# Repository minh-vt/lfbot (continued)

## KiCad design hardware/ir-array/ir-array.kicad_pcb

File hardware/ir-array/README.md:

# IR array — tám mắt, dải cong IR-03

> **Thiết kế PCB đã dừng theo [ADR-019](../../docs/decisions/ADR-019-module-based-hardware.md).** Nội dung bên dưới là lịch sử, không phải hướng dẫn lắp hiện hành. Dùng [pin map module](../wiring.md); không gia công hoặc đấu dây theo bảng cũ. Giữ source và thư viện chờ duyệt cleanup.

**IR-03 placement được người dùng duyệt G1 ngày 2026-10-19; chưa phát hành gia công.** Hai vai bo tròn, không tai đầu/bậc giữa; header đực 1×12 gần mép trong; giữ8 TCRT5000 và mạch headroom IR-02. Schematic giữ nguyên. Outline option02 đã được khớp lại vào footprint native qua KiCad IPC; placement sensor/header không đổi. Board nguồn chưa route. Một recovery candidate bị đổi thành bản có218 cung tròn và35 lỗi DRC; đã tái tạo bản sạch rồi thử reroute riêng +3V3, tăng margin +3V3 từ0.592 lên0.9005mm. Nhưng bản thử thêm3 via-in-pad SMD và EMC analyzer báo GP-001 regression cho /IR1; dù native DRC0 lỗi/0 unconnected, bản này **không được chọn làm candidate tốt hơn hoặc nhập vào nguồn**. Track /IR7 vẫn0.700mm; còn26 board warnings/42 parity warnings. Xem [review và log quyết định](OPTIMIZATION_REVIEW.md), [lịch sử outline/routing](REVIEW.md). G2/fabrication chưa duyệt.

Yêu cầu hiện tại: tám TCRT5000 trên một cung trong mặt phẳng PCB, các mặt đọc
cùng hướng xuống sàn và cùng độ cao; tối ưu diện tích PCB. Người dùng đã chốt
hai PCB tự thiết kế, **rời vật lý**: thân và đầu IR cong. Không còn ưu tiên
một PCB liền của M02. Cách gá theo [spec](../SPEC.md) và [tickets](../TICKETS.md),
chưa freeze trong bản CAD này. Gá caster in 3D do người dùng thiết kế.
BOM mua hàng vẫn là [HARDWARE_BOM.csv](../../docs/HARDWARE_BOM.csv).

## Giao diện tám mắt đã chọn

J1=`PinHeader_1x12_P2.54mm_Vertical` (header đực thẳng, 1×12). Số chân dưới đây là số pad,
không phải thứ tự nhìn từ đầu dây. Header không có khóa; đánh dấu pad1 ở cả hai
đầu và continuity-test harness trước cấp nguồn, không đoán theo màu dây. Bảng
GPIO dưới đây khớp netlist [MAIN hiện tại](../main/main.kicad_sch), với số chân
DevKitC-1 tham chiếu; chưa xác minh pinout/nguồn của TDM2533 thực tế hoặc
firmware. Không coi bảng là dây robot đã được đấu thử.

| J1 IR | Net | GPIO / ADC1 | Header DevKit chuẩn |
|---|---|---|---|
| 1 | +5V | Nguồn LED từ buck; không nối ADC | J1.21 (rail5V; phải kiểm tra backfeed hệ thống) |
| 2 | +3V3 | Nguồn pull-up từ DevKit | J1.1 hoặc J1.2 |
| 3 | GND | Ground chung | J1.22 hoặc J3.1 |
| 4 | LED_EN | GPIO21, active high | J3.18 |
| 5 | IR0 | GPIO1 / CH0 | J3.4 |
| 6 | IR1 | GPIO2 / CH1 | J3.5 |
| 7 | IR2 | GPIO4 / CH3 | J1.4 |
| 8 | IR3 | GPIO5 / CH4 | J1.5 |
| 9 | IR4 | GPIO6 / CH5 | J1.6 |
| 10 | IR5 | GPIO7 / CH6 | J1.7 |
| 11 | IR6 | GPIO8 / CH7 | J1.12 |
| 12 | IR7 | GPIO9 / CH8 | J1.15 |

BAT_ADC dành GPIO10/ADC1_CH9, headerJ1.16, **không đi qua cáp IR**. Đưa nó
vào cùng pattern continuous gồm9 kênh; không chạy oneshot trên ADC1 đang
continuous. Không dùng ADC2 DMA hoặc GPIO3 cho IR/BAT. MAIN để GPIO19/20
cho USB; không dùng GPIO0/3/45/46 và GPIO35…37 dành cho bộ nhớ Octal.
GPIO11…14 điều khiển hai A4950; GPIO15…18 tới cầu encoder R12…R15 mặc định
DNP. I²C dùng GPIO39/38 qua J5.3/J5.4; GPIO42/41 ra J5.5/J5.6. Đối chiếu
pinout module ToF trước khi đấu. GPIO38 có thể nối RGB LED trên một số
DevKit; phải xác nhận revision TDM2533, không bật LED trên chân đang dùng
cho I²C. Không lấy phân bổ GPIO cũ trong tài liệu IR để cấu hình MAIN.

### Headroom ADC và nguồn

R9…R16=10k/1% kéo lên3V3; **R19…R26=33k/1% kéo từng IRi xuống GND**.
Không dùng bộ chia chung cho tám mắt vì tải mỗi mắt sẽ làm lệch các mắt khác.
Ở dòng thu bằng0: `V_IR = V3V3 × 33/(10+33)`; danh định2.533 V.
Với rail thiết kế không vượt3.6 V và cả hai R±1%, góc xấu nhất nhỏ hơn2.776 V,
so với biên2.9 V trong vùng ADC được Espressif đặc tả. Đây không phải bảo vệ
khi đấu nhầm5V hoặc chứng minh nhiễu motor đã được kiểm soát.

Trở Thevenin danh định7.674k thay vì10k: gain dòng–áp giảm khoảng23.3%.
Giá trị này sửa headroom, **không chứng minh gain tối ưu hoặc hết bão hòa
phototransistor**. Dòng thu mạnh vẫn có thể ép IR xuống sát0. Phải kiểm tra
hai pha off/on không clipping; không lấy phép trừ để cứu mẫu đã bão hòa.

Không thêm100nF vào mỗi IR: RC với7.674k đã0.767 ms, không phù hợp ngân sách
settling250µs dưới đây. C1/C2/C3 chỉ là tụ rail. Chưa chốt tụ/filter ADC hoặc
buffer khi chưa có dữ liệu harness/SAR; nếu settling không đạt phải sửa thiết
kế/timing, không tự coi nhiều mẫu liên tiếp là đã ổn định.

R1…R8=220Ω, Q1 vẫn AO3400A. Ước tính Vf1.25 V cho khoảng17mA/mắt và136mA
cả tám; đây không phải dòng đo. Buck/harness phải cấp được dòng LED cùng
logic trong khi giữ rail; tụ10µF không tự cấp toàn bộ xung LED. R18 kéo gate
về GND lúc reset; bắt đầu capture với LED_EN thấp.

### Ngân sách capture để triển khai sau

Mục tiêu thiết kế, **chưa triển khai hoặc đo**: ADC1 continuous72kSa/s tổng,
9 kênh theo bảng + BAT, ATTEN3/12bit và calibration từng chip. Một scan125µs;
mỗi kênh8kSa/s. Hai pha trong chu kỳ2ms:

| Pha | Bỏ sau cạnh LED | Thu | Thời gian conversion |
|---|---|---|---|
| Off | 2 scan =250µs | 4 scan đầy đủ =500µs | 750µs |
| On | 2 scan =250µs | 4 scan đầy đủ =500µs | 750µs |

Còn500µs trong chu kỳ2ms cho lịch/biên DMA/thu thập/xử lý. Chuyển pha theo
mốc thời gian, không giả định LED đổi đúng cạnh DMA. Bỏ mọi scan chạm cạnh,
chỉ ghép off/on đủ8 mắt trong cùng chu kỳ và đúng channel ID. BAT đọc trong
pattern, lọc riêng; không đổi pattern hoặc dừng ADC để đọc pin.

72k nằm trong giới hạn header IDFv5.5.1 tham chiếu; phải kiểm tra version và
nhịp hiệu dụng thật khi triển khai.250µs là budget, không phải thời gian đáp
ứng TCRT đã đo. Bảo toàn timestamp/age, clipping, overflow và deadline; nếu
không đạt phải báo mẫu không hợp lệ/đi an toàn, không tái dùng frame cũ như mới.
Không block hoặc xử lý điều khiển trong ISR. ESP32/HIL vẫn là công việc riêng.

Nguồn pin/ADC: [DevKitC-1 v1.1](https://docs.espressif.com/projects/esp-dev-kits/en/latest/esp32s3/esp32-s3-devkitc-1/user_guide_v1.1.html),
[ADC continuous](https://docs.espressif.com/projects/esp-idf/en/stable/esp32s3/api-reference/peripherals/adc/adc_continuous.html),
ESP32-S3 Datasheet Table2-8/5-5/5-6; bản tải và phép tính ở recovery của review.

## Căn cứ thiết kế

- [Luật thi đấu](../../docs/manual.md), Điều 3.2 và 4.2: robot tối đa
  160 × 160 mm; line rộng 20 mm. Hai ràng buộc này không xác định bán kính array,
  vùng bắt lại line hoặc lookahead tối ưu.
- [Vishay TCRT5000, document 83760](https://www.vishay.com/docs/83760/tcrt5000.pdf),
  bản tham chiếu [lưu trong project](../libs/datasheets/TCRT5000_Vishay.pdf):
  hình kích thước/footprint xác định thân khoảng 10,2 × 5,8 mm, vị trí bốn chân
  và các lỗ cho ngàm. Fig. 9 cho thấy tín hiệu phụ thuộc khoảng cách tới bề mặt
  trong điều kiện thử của hãng. Không có bán kính array tối ưu hoặc đường kính
  vùng đọc có thể mặc định dùng cho lô hàng mua tại shop.
- [Pololu QTRSensors Methods & Usage Notes](https://www.pololu.com/docs/0J19/3):
  khoảng cách cảm biến phải phù hợp bề rộng line để ước lượng vị trí có tính đơn
  điệu; hiệu chuẩn từng kênh và đọc LED on/off giúp xử lý sai khác/ánh sáng nền.
  Đây là tài liệu QTR, không phải thông số quang học của TCRT5000. Công thức
  trung bình chỉ số trong ví dụ không tự trở thành tọa độ hình học cho array cong.
- [Pololu Additional Considerations](https://www.pololu.com/docs/0J12/7): độ cao
  tăng và IR môi trường làm giảm tương phản; che sáng có thể cần thiết. Không
  chuyển giới hạn độ cao của QTR sang TCRT5000. Phần che sáng không được trở
  thành chân trượt chạm sàn, theo luật thi đấu.
- [Coulter, CMU-RI-TR-92-01 (1992)](https://publications.ri.cmu.edu/storage/publications/pub_files/pub3/coulter_r_craig_1992_1/coulter_r_craig_1992_1.pdf),
  §2 và §4.1–4.3: hình học lookahead và đánh đổi trong pure pursuit. Ngay cả
  độ cong đường đi cũng không xác định một lookahead tối ưu duy nhất. Báo cáo
  không thử nghiệm TCRT5000, không chứng minh array cong nhanh hơn array thẳng,
  và không có nghĩa firmware LF-Bot đã dùng pure pursuit.

## Tính cung thay vì chọn bán kính tùy ý

Một phương án có ý nghĩa hình học là cung có tâm tại trung điểm trục hai bánh.
Đó là **lựa chọn thiết kế** để các vị trí danh định có cùng khoảng cách tới trục,
không phải kết luận rằng phương án này tối ưu thời gian thi đấu.

Với trục x hướng trước, y hướng ngang, bán kính R và góc bố trí θᵢ:

```
xᵢ = R cos(θᵢ)
yᵢ = R sin(θᵢ)
θᵢ = (i − 3,5) Δθ, i = 0…7   [nếu chọn chia đều góc]
```

Nếu p là khoảng cách dây cung giữa hai vị trí kề nhau:

```
Δθ = 2 asin(p / (2R))
W = 2R sin(3,5 Δθ)
```

Nếu xác định trước bề rộng dây cung W và độ võng h tính từ đỉnh cung danh định
đến dây nối hai vị trí ngoài cùng (cung trước không vượt nửa vòng: 0 < h ≤ W/2):

```
R = W² / (8h) + h/2
h = R − sqrt(R² − (W/2)²)
```

Đây là hệ thức hình học, không phải công thức tối ưu điều khiển. Với tám mắt
chia đối xứng sẽ không có mắt nằm đúng tại đỉnh cung; hai mắt giữa ở ±Δθ/2.
Tâm bố trí footprint cũng không mặc nhiên là tâm vùng nhạy quang học thực tế.
Pitch 12 mm của layout thẳng cũ chưa phải yêu cầu đã chứng minh cho array cong.

Không lấy bán kính đường đua làm bán kính array. Không suy R từ riêng bề rộng
line 20 mm, kích thước tối đa robot hoặc một PCB mẫu trên mạng.

## Tối ưu diện tích

Dùng outline lưỡi liềm liền mạch theo vùng cảm biến và giao diện, không giữ nguyên tấm chữ nhật 100 × 30 mm rồi chỉ dời cảm biến. IR-03 giữ LED ở r74.5; pull-up/shunt chia hàng phía ngoài, Q1/gate gần mép trái; header đực gần mép trong. Không xung đột ngàm, vùng hàn,
lỗ gá hoặc hy sinh đường hồi LED/GND để giảm diện tích.

So sánh cả diện tích vật liệu và bounding box; không giảm diện tích bằng cách
bỏ khoảng hở chế tạo, độ bền vùng lỗ gá hoặc chỗ đi dây. Phải kiểm tra các thân
linh kiện đã xoay và toàn bộ footprint/lỗ ngàm, không chỉ khoảng cách tâm.
Đổi hướng thân TCRT5000 còn đổi hướng cặp phát/thu; không mặc định nó chỉ là
một thao tác đóng gói cơ khí.

## Đầu IR-03 theo ảnh tham khảo

[Ảnh người dùng](../mechanical/references/ir-strip-reference.png) là mẫu bố
cục, không phải nguồn kích thước/pinout. [M03-IR03](../MECHANICAL.md) giữ đầu
**tách rời vật lý** khỏi thân bằng hai liên kết G10 dogleg không đồng.
[Bản vẽ](../mechanical/layout.svg) và [tọa độ nguồn](../mechanical/layout.json)
đã cập nhật outline lưỡi liềm, giữ tọa độ lỗ/slot, liên kết và giao diện header; không đổi carrier CAD.

Nhìn từ F.Cu/mặt trên, phía trước hướng lên: `boardX=100−vehicleY`,
`boardY=137.5−vehicleX`, góc TCRT B.Cu=`90+θ`. U1/IR0 ở phía phải robot
(y−28), U8/IR7 ở phía trái(y+28). IR-02 đã sửa phép đổi dấu Y trước đây;
không mirror kênh thêm lần nữa chỉ vì đang xem mặt B.Cu từ dưới.

- R80/span56; bước góc5.85352°, pitch dây cung8.16950. R tăng để dành khe
  giữa hai PCB, không phải kết luận bán kính tối ưu điều khiển.
- Cung ngoài R88/±24°, biên sau cong nông, không tai/bậc giữa. Bao ngoài
  **85×24.5 mm**; khe thân21.5 danh định/18.5 khi lùi3. Diện tích outline
  danh định khoảng1703 mm² trước trừ lỗ; không suy giá từ diện tích. Gá vẫn cho dịch−3…+2.
- PCB đầu dày mục tiêu1.6, đáy9.5. d2.5 danh định, d2…3.5 bằng shim1.4…2.9;
  tính theo mốc7 mm, phù hợp working distance d trong Fig.3 Vishay nếu mặt chuẩn A
  sát PCB. Khe tới mốc vòm6.3 mm là3.2 mm, **không phải lý do tự hạ PCB0.7**.
  Ghi rõ datum, kiểm tra cách ngồi/clip và dung sai trước freeze shim; xem R03.
- Tám TCRT ở B.Cu, R/C và header đực J1 ở F.Cu; hai lỗ M2 tại **(70.5,±38.5)**. Các tọa độ/góc là
  mốc thân10.2×5.8, chưa phải spot quang hoặc gốc pad1. Đã đọc lại pad qua IPC
  sau phép lật B.Cu, đối chiếu đủ105 pad điện/39 linh kiện với netlist IR-03;
  chưa có đo quang.
- Dùng footprint stock `OptoDevice:Vishay_TCRT5000`; symbol local đánh số
  1=C,2=E,3=K,4=A. Không đổi trực tiếp sang CNY70 có thứ tự chân khác.

Biên native hiện gồm **226 đoạn thẳng lấy mẫu** trong `IR_Array:Outline_IR03`, khớp contour SVG option02; điểm giữa mép sau là vehicle x64.75 mm. MP1 được refresh và lưu qua IPC khi board đang mở. DRC placement hiện có83 unconnected,26 cảnh báo board (8 library mismatch,16 silk-over-copper,2 silk-overlap) và42 parity warnings; chưa có invalid outline, copper-edge clearance, pad hoặc hole conflict mới. Board nguồn còn0 track/via/zone; chưa áp dụng routing.
Sau chốt placement: routing sau G1 → ERC/netlist/DRC → review pad/mask/drill/
cơ khí → bộ xuất.
Đọc LED-off/on không phục hồi dữ liệu đã bão hòa vì ánh sáng môi trường.

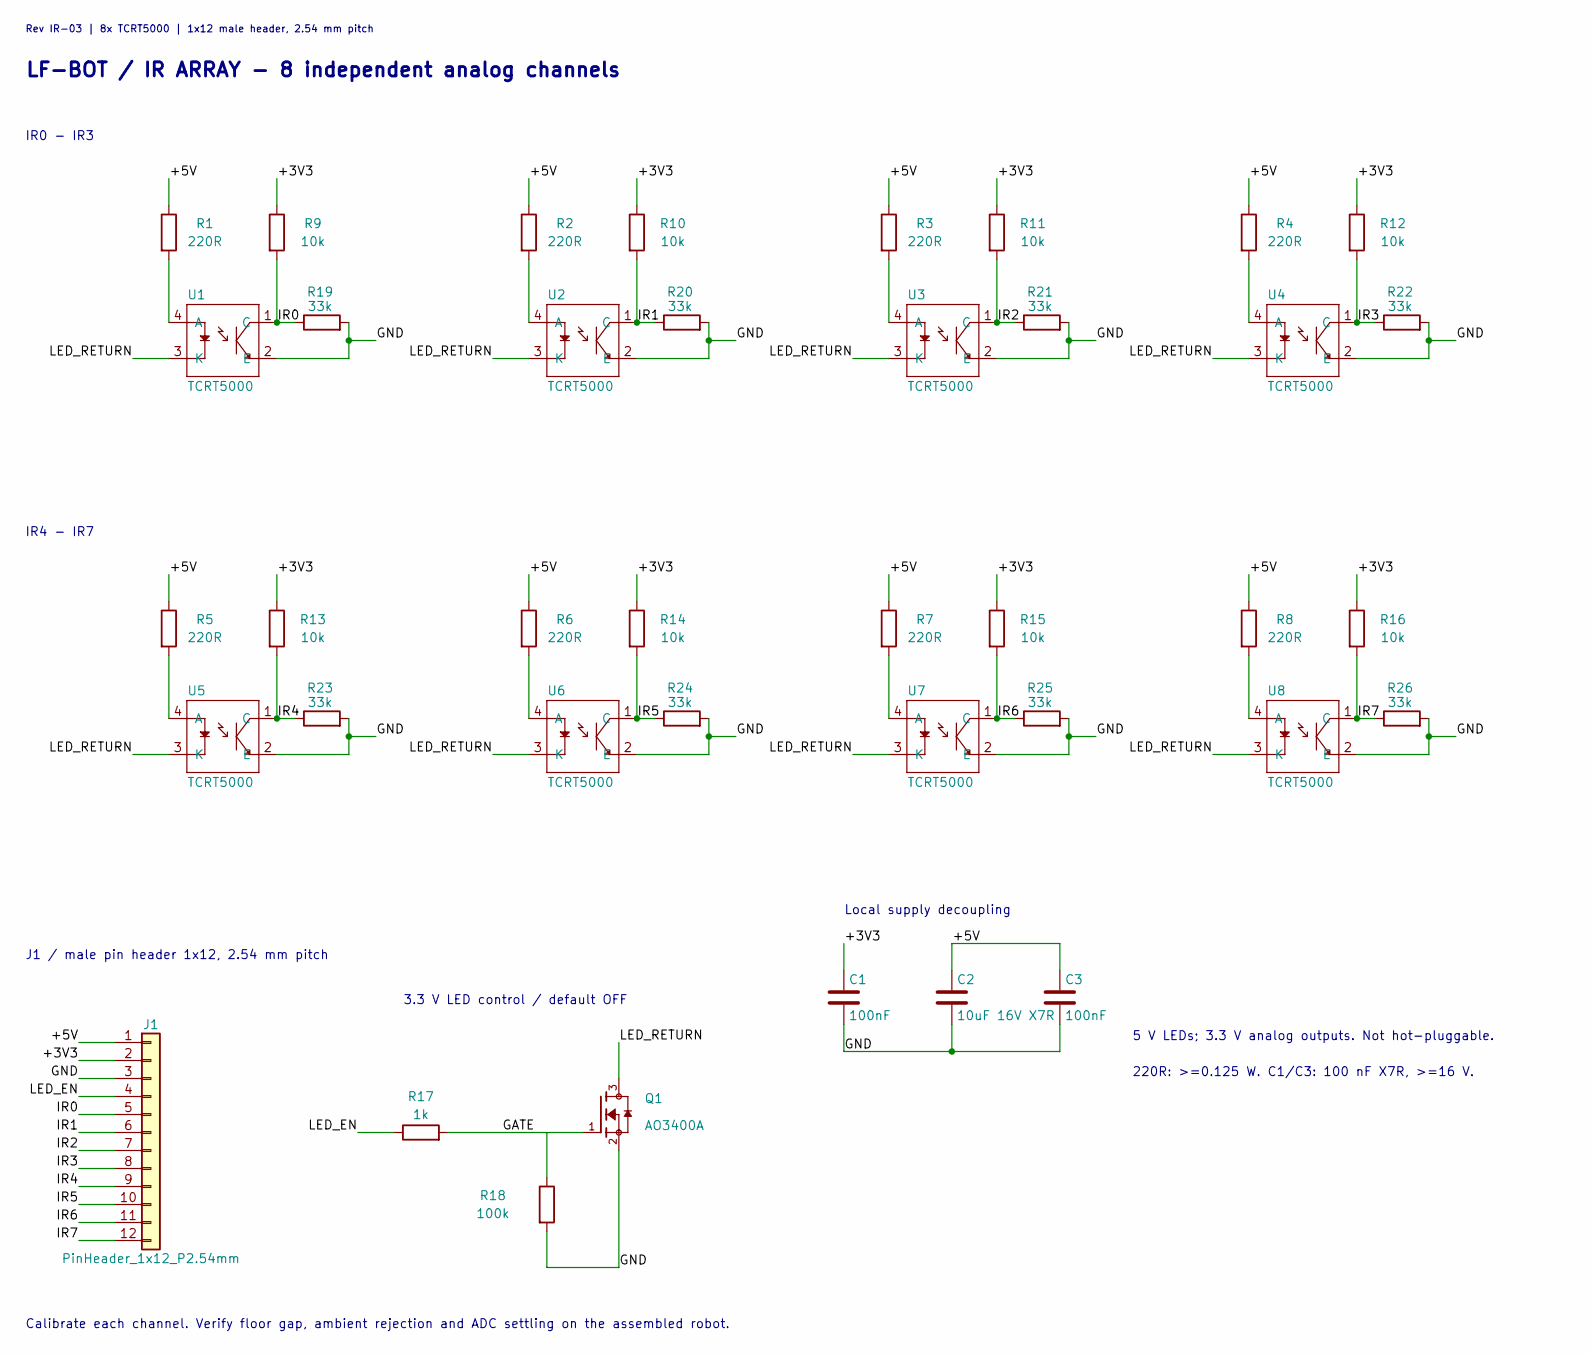
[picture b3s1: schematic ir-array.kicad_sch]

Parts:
C1, C3: 100nF; C_0805_2012Metric
C2: 10uF 16V X7R; C_1206_3216Metric
J1: PinHeader_1x12_P2.54mm; PinHeader_1x12_P2.54mm_Vertical
Q1: AO3400A; SOT-23
R1, R2, R3, R4, R5, R6, R7, R8: 220R; R_0805_2012Metric
R9, R10, R11, R12, R13, R14, R15, R16: 10k; R_0805_2012Metric; Tolerance 1%
R17: 1k; R_0805_2012Metric
R18: 100k; R_0805_2012Metric
R19, R20, R21, R22, R23, R24, R25, R26: 33k; R_0805_2012Metric; Tolerance 1%
U1, U2, U3, U4, U5, U6, U7, U8: TCRT5000; Vishay_TCRT5000

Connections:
/+3V3: C1.1, J1.2, R9.1, R10.1, R11.1, R12.1, R13.1, R14.1, R15.1, R16.1
/+5V: C2.1, C3.1, J1.1, R1.1, R2.1, R3.1, R4.1, R5.1, R6.1, R7.1, R8.1
/GATE: Q1.1, R17.2, R18.1
/GND: C1.2, C2.2, C3.2, J1.3, Q1.2, R18.2, R19.2, R20.2, R21.2, R22.2, R23.2, R24.2, R25.2, R26.2, U1.2 (E), U2.2 (E), U3.2 (E), U4.2 (E), U5.2 (E), U6.2 (E), U7.2 (E), U8.2 (E)
/IR0: J1.5, R9.2, R19.1, U1.1 (C)
/IR1: J1.6, R10.2, R20.1, U2.1 (C)
/IR2: J1.7, R11.2, R21.1, U3.1 (C)
/IR3: J1.8, R12.2, R22.1, U4.1 (C)
/IR4: J1.9, R13.2, R23.1, U5.1 (C)
/IR5: J1.10, R14.2, R24.1, U6.1 (C)
/IR6: J1.11, R15.2, R25.1, U7.1 (C)
/IR7: J1.12, R16.2, R26.1, U8.1 (C)
/LED_EN: J1.4, R17.1
/LED_RETURN: Q1.3, U1.3 (K), U2.3 (K), U3.3 (K), U4.3 (K), U5.3 (K), U6.3 (K), U7.3 (K), U8.3 (K)
unnamed: R1.2, U1.4 (A)
unnamed: R2.2, U2.4 (A)
unnamed: R3.2, U3.4 (A)
unnamed: R4.2, U4.4 (A)
unnamed: R5.2, U5.4 (A)
unnamed: R6.2, U6.4 (A)
unnamed: R7.2, U7.4 (A)
unnamed: R8.2, U8.4 (A)

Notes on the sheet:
LF-BOT / IR ARRAY - 8 independent analog channels
Rev IR-03 | 8x TCRT5000 | 1x12 male header, 2.54 mm pitch
5 V LEDs; 3.3 V analog outputs. Not hot-pluggable.
220R: >=0.125 W. C1/C3: 100 nF X7R, >=16 V.
J1 / male pin header 1x12, 2.54 mm pitch
3.3 V LED control / default OFF
IR0 - IR3
IR4 - IR7
Local supply decoupling
Calibrate each channel. Verify floor gap, ambient rejection and ADC settling on the assembled robot.

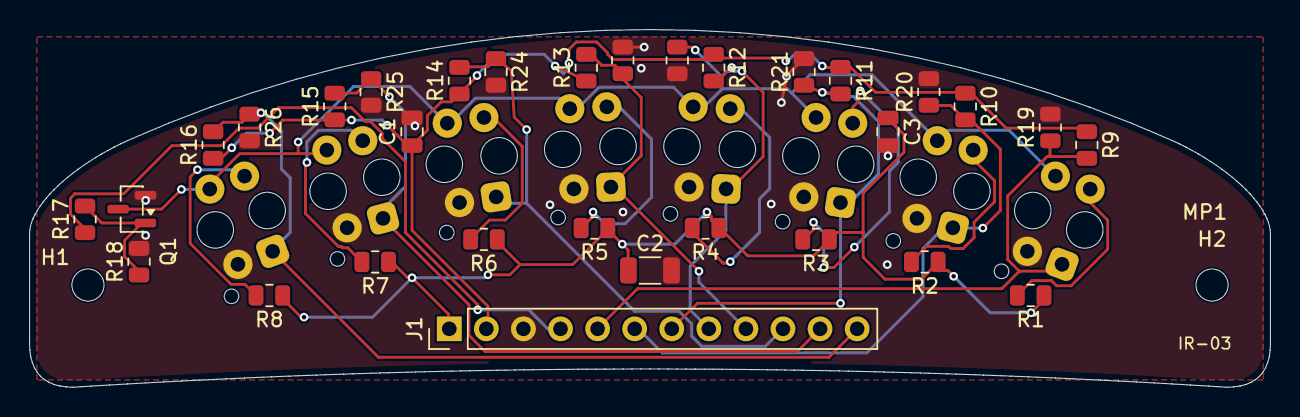
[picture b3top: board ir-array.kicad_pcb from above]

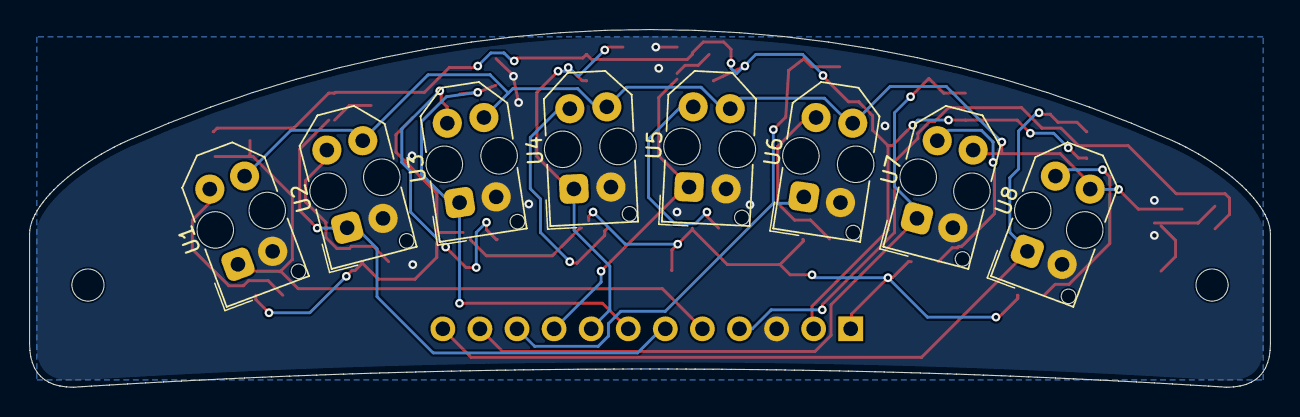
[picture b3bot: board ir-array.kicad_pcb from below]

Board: 2 copper layers, 85.0 x 24.5 mm, 42 parts (8 on the bottom side), 22 nets.

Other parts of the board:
H1, H2: MountingHole_2.2mm_M2
MP1: Outline_IR03

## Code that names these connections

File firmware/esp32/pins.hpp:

#pragma once

// Every pin the firmware touches, in one place. Source: hardware/wiring.md
// (single-sided base board v0.7). The board also wires BTN_2 (GPIO12) and IMU INT
// (GPIO13); nothing drives them yet.
namespace lf::esp32::pins {

// The bar's IR pin reaches GPIO18 only with jumper J4 on that position.
inline constexpr int kIrCtrl = 18;
// What that pin does to the bar. NOT KNOWN YET (wiring.md: "điều khiển LED?"): find
// out on the board with the console's `irctl` and `monitor`, then set it. kNotUsed
// leaves GPIO18 an input; the other two make the ADC read each eye with its LED on
// and off and publish the difference, which cancels room light.
enum class IrCtrl { kNotUsed, kLedOnHigh, kLedOnLow };
inline constexpr IrCtrl kIrCtrlWiring = IrCtrl::kNotUsed;

// IR D1..D8, left to right on the bar: GPIO10, 9, 3, 8, 7, 6, 5, 4.
// On ADC1, channel = GPIO - 1.
inline constexpr int kIrAdcChannel[8] = {9, 8, 2, 7, 6, 5, 4, 3};
inline constexpr int kBatteryAdcChannel = 0;  // GPIO1
inline constexpr int kMotorLeftIn1 = 38;
inline constexpr int kMotorLeftIn2 = 39;
inline constexpr int kMotorRightIn1 = 41;
inline constexpr int kMotorRightIn2 = 42;
inline constexpr int kI2cSda = 15;
inline constexpr int kI2cScl = 16;
inline constexpr int kEncoderLeftA = 21;
inline constexpr int kEncoderLeftB = 47;
inline constexpr int kEncoderRightA = 40;
inline constexpr int kEncoderRightB = 2;
inline constexpr int kButton = 11;  // START
inline constexpr int kTofShutdown = 17;
inline constexpr int kStatusLed = 48;  // RGB LED on the devkit

}  // namespace lf::esp32::pins
